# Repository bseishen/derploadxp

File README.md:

derploadxp
==========

Electronic Dummy Load

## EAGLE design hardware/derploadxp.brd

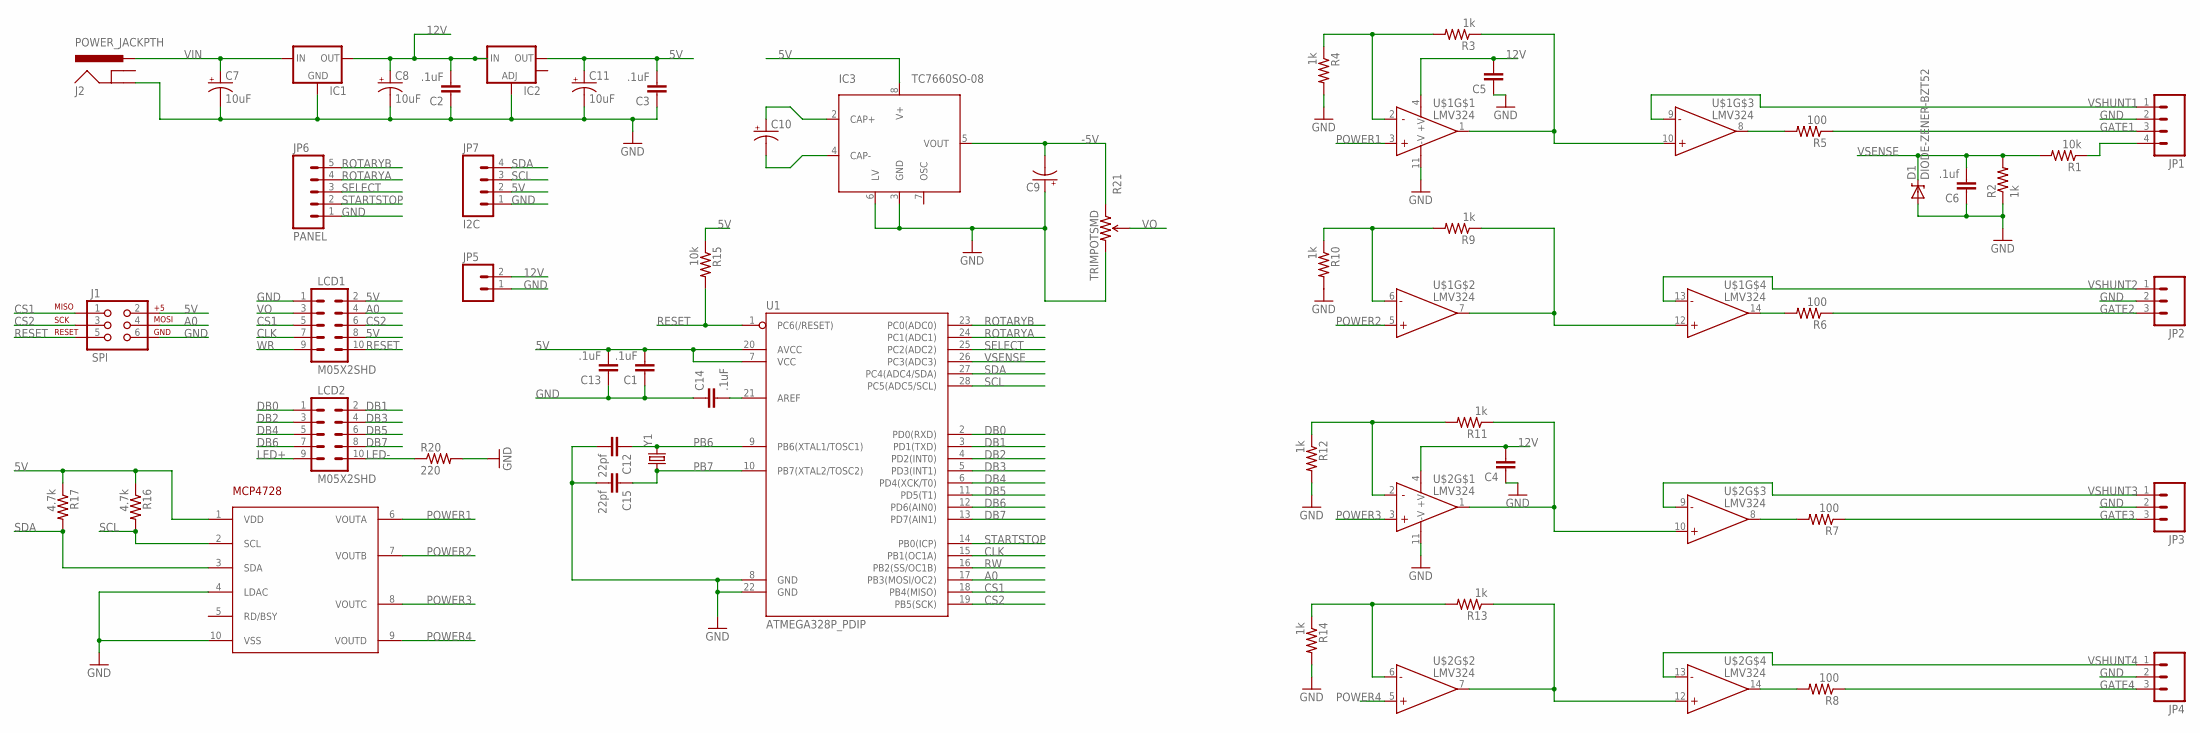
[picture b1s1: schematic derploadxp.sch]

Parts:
C1, C2, C3, C13, C14: .1uF; 0805
C4, C5: CAP0805; 0805
C6: .1uf; 0805
C7, C8, C11: 10uF; PANASONIC_C
C9, C10: CAP_POLC; PANASONIC_C
C12, C15: 22pf; 0805
D1: DIODE-ZENER-BZT52; SOD-323
IC1: V_REG_78XXSINK; TO220-IGO
IC2: V_REG_LM1117SOT223; SOT223
IC3: TC7660SO-08; SO-08
J1: SPI; 2X3-NS
J2: POWER_JACKPTH; POWER_JACK_PTH
JP1: M04LOCK; 1X04_LOCK
JP2, JP3, JP4: M03LOCK; 1X03_LOCK
JP5: M02LOCK; 1X02_LOCK
JP6: PANEL; 1X05_LOCK
JP7: I2C; 1X04_LOCK
LCD1, LCD2: M05X2SHD; 2X5-SHROUDED
R1, R15: 10k; 0805
R2, R3, R4, R9, R10, R11, R12, R13, R14: 1k; 0805
R5, R6, R7, R8: 100; 0805
R16, R17: 4.7k; 0805
R20: 220; 0805
R21: TRIMPOTSMD; TRIMPOT-3MM
U1: ATMEGA328P_PDIP; DIL28-3
U$1, U$2: LMV324; SO014
U$4: MCP4728; MSOP10
Y1: CRYSTALSMD; HC49UP

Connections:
5V: C1.2, C3.2, C11.+, C13.2, IC2.2 (OUT), IC3.8 (V+), J1.2, JP7.2, LCD1.2, LCD1.8, R15.1, R16.1, R17.1, U1.7 (VCC), U1.20 (AVCC), U$4.1 (VDD)
12V: C2.2, C4.2, C5.2, C8.+, IC1.OUT, IC2.3 (IN), JP5.2, U$1.4 (+V), U$2.4 (+V)
-5V: C9.-, IC3.5 (VOUT), R21.1 (CCW)
A0: J1.4, LCD1.4, U1.17 (PB3(MOSI/OC2))
CLK: LCD1.7, U1.15 (PB1(OC1A))
CS1: J1.1, LCD1.5, U1.18 (PB4(MISO))
CS2: J1.3, LCD1.6, U1.19 (PB5(SCK))
DB0: LCD2.1, U1.2 (PD0(RXD))
DB1: LCD2.2, U1.3 (PD1(TXD))
DB2: LCD2.3, U1.4 (PD2(INT0))
DB3: LCD2.4, U1.5 (PD3(INT1))
DB4: LCD2.5, U1.6 (PD4(XCK/T0))
DB5: LCD2.6, U1.11 (PD5(T1))
DB6: LCD2.7, U1.12 (PD6(AIN0))
DB7: LCD2.8, U1.13 (PD7(AIN1))
GATE1: JP1.3, R5.1
GATE2: JP2.3, R6.1
GATE3: JP3.3, R7.1
GATE4: JP4.3, R8.1
GND: C1.1, C2.1, C3.1, C4.1, C5.1, C6.1, C7.-, C8.-, C9.+, C11.-, C12.2, C13.1, C14.1, C15.2, D1.2 (A), IC1.GND, IC2.1 (ADJ), IC3.3 (GND), IC3.6 (LV), J1.6, J2.GND, JP1.2, JP2.2, JP3.2, JP4.2, JP5.1, JP6.1, JP7.1, LCD1.1, R2.1, R4.2, R10.2, R12.2, R14.2, R20.2, R21.3 (CW), U1.8 (GND), U1.22 (GND), U$1.11 (-V), U$2.11 (-V), U$4.4 (LDAC), U$4.10 (VSS)
LED+: LCD2.9
LED-: LCD2.10, R20.1
unnamed: JP1.4, R1.1
unnamed: C10.+, IC3.2 (CAP+)
unnamed: R5.2, U$1.8 (OUT)
unnamed: C10.-, IC3.4 (CAP-)
unnamed: R3.1, U$1.1 (OUT), U$1.10 (+IN)
unnamed: R9.2, R10.1, U$1.6 (-IN)
unnamed: R3.2, R4.1, U$1.2 (-IN)
unnamed: R6.2, U$1.14 (OUT)
unnamed: R8.2, U$2.14 (OUT)
unnamed: R7.2, U$2.8 (OUT)
unnamed: C14.2, U1.21 (AREF)
unnamed: R9.1, U$1.7 (OUT), U$1.12 (+IN)
unnamed: R11.2, R12.1, U$2.2 (-IN)
unnamed: R13.2, R14.1, U$2.6 (-IN)
unnamed: R13.1, U$2.7 (OUT), U$2.12 (+IN)
unnamed: R11.1, U$2.1 (OUT), U$2.10 (+IN)
PB6: C12.1, U1.9 (PB6(XTAL1/TOSC1)), Y1.2
PB7: C15.1, U1.10 (PB7(XTAL2/TOSC2)), Y1.1
POWER1: U$1.3 (+IN), U$4.6 (VOUTA)
POWER2: U$1.5 (+IN), U$4.7 (VOUTB)
POWER3: U$2.3 (+IN), U$4.8 (VOUTC)
POWER4: U$2.5 (+IN), U$4.9 (VOUTD)
RESET: J1.5, LCD1.10, R15.2, U1.1 (PC6(/RESET))
ROTARYA: JP6.4, U1.24 (PC1(ADC1))
ROTARYB: JP6.5, U1.23 (PC0(ADC0))
RW: U1.16 (PB2(SS/OC1B))
SCL: JP7.3, R16.2, U1.28 (PC5(ADC5/SCL)), U$4.2 (SCL)
SDA: JP7.4, R17.2, U1.27 (PC4(ADC4/SDA)), U$4.3 (SDA)
SELECT: JP6.3, U1.25 (PC2(ADC2))
STARTSTOP: JP6.2, U1.14 (PB0(ICP))
VIN: C7.+, IC1.IN, J2.PWR
VO: LCD1.3, R21.2 (WIPER)
VSENSE: C6.2, D1.1 (C), R1.2, R2.2, U1.26 (PC3(ADC3))
VSHUNT1: JP1.1, U$1.9 (-IN)
VSHUNT2: JP2.1, U$1.13 (-IN)
VSHUNT3: JP3.1, U$2.9 (-IN)
VSHUNT4: JP4.1, U$2.13 (-IN)
WR: LCD1.9

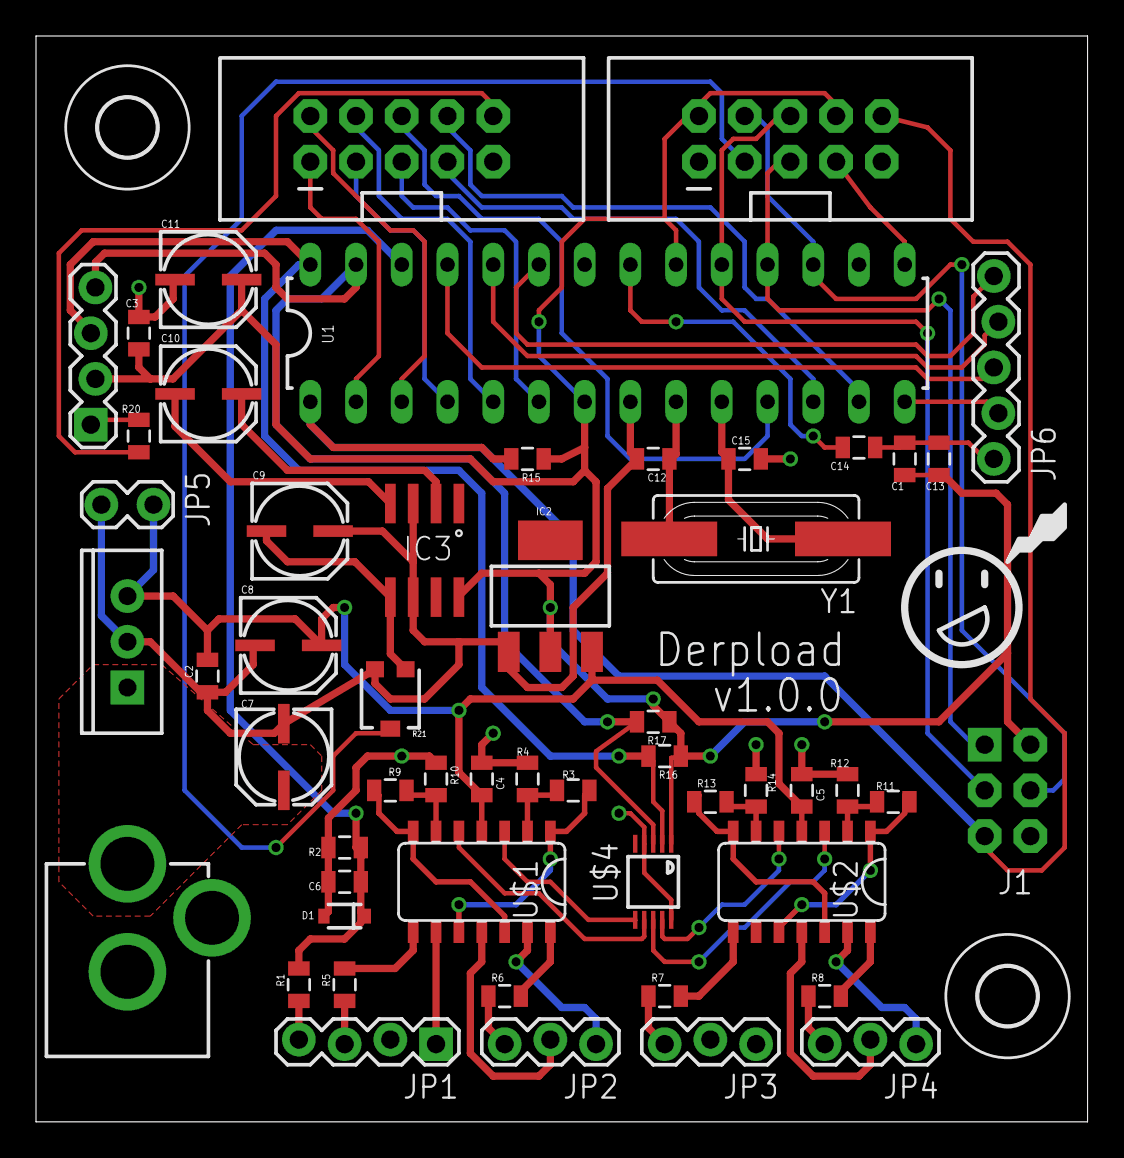
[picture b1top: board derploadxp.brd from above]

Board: 2 copper layers, 58.4 x 60.3 mm, 56 parts (0 on the bottom side), 57 nets.

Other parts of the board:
U$5, U$7: 3,2

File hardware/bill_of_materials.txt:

Partlist

Exported from derploadxp.brd at 10/17/13 11:35 PM

EAGLE Version 6.4.0 Copyright (c) 1988-2013 CadSoft

Assembly variant: 

Part     Value             Package        Library                    Position (inch)       Orientation

C1       .1uF              0805           SparkFun-Passives          (1.9 1.45)            R270
C2       .1uF              0805           SparkFun-Passives          (0.375 0.975)         R90
C3       .1uF              0805           SparkFun-Passives          (0.225 1.725)         R270
C4                         0805           SparkFun-Passives          (0.975 0.75)          R270
C5                         0805           SparkFun-Passives          (1.675 0.725)         R270
C6       .1uf              0805           SparkFun-Passives          (0.675 0.525)         R0
C7       10uF              PANASONIC_C    SparkFun-Capacitors        (0.55 0.8)            R270
C8       10uF              PANASONIC_C    SparkFun-Capacitors        (0.55 1.05)           R0
C9                         PANASONIC_C    SparkFun-Capacitors        (0.575 1.3)           R0
C10                        PANASONIC_C    SparkFun-Capacitors        (0.375 1.6)           R0
C11      10uF              PANASONIC_C    SparkFun-Capacitors        (0.375 1.85)          R0
C12      22pf              0805           SparkFun-Passives          (1.35 1.45)           R180
C13      .1uF              0805           SparkFun-Passives          (1.975 1.45)          R270
C14      .1uF              0805           SparkFun-Passives          (1.8 1.475)           R180
C15      22pf              0805           SparkFun-Passives          (1.55 1.45)           R0
D1       DIODE-ZENER-BZT52 SOD-323        SparkFun-DiscreteSemi      (0.675 0.45)          R180
IC1                        TO220-IGO      SparkFun-PowerIC           (0.2 1.05)            R90
IC2                        SOT223         SparkFun-PowerIC           (1.125 1.15)          R0
IC3      TC7660SO-08       SO-08          microchip_tc7660           (0.85 1.25)           R180
J1       SPI               2X3-NS         SparkFun-Connectors        (2.125 0.725)         R270
J2       POWER_JACKPTH     POWER_JACK_PTH SparkFun-Connectors        (0.2 0.025)           R0
JP1                        1X04_LOCK      SparkFun-Connectors        (0.875 0.175)         R180
JP2                        1X03_LOCK      SparkFun-Connectors        (1.225 0.175)         R180
JP3                        1X03_LOCK      SparkFun-Connectors        (1.575 0.175)         R180
JP4                        1X03_LOCK      SparkFun-Connectors        (1.925 0.175)         R180
JP5                        1X02_LOCK      SparkFun-Connectors        (0.15 1.35)           R0
JP6      PANEL             1X05_LOCK      SparkFun-Connectors        (2.1 1.45)            R90
JP7      I2C               1X04_LOCK      SparkFun-Connectors        (0.125 1.525)         R90
LCD1     M05X2SHD          2X5-SHROUDED   SparkFun-Connectors        (1.65 2.15)           R90
LCD2     M05X2SHD          2X5-SHROUDED   SparkFun-Connectors        (0.8 2.15)            R90
R1       10k               0805           SparkFun-Passives          (0.575 0.3)           R90
R2       1k                0805           SparkFun-Passives          (0.675 0.6)           R0
R3       1k                0805           SparkFun-Passives          (1.175 0.725)         R180
R4       1k                0805           SparkFun-Passives          (1.075 0.75)          R90
R5       100               0805           SparkFun-Passives          (0.675 0.3)           R90
R6       100               0805           SparkFun-Passives          (1.025 0.275)         R0
R7       100               0805           SparkFun-Passives          (1.375 0.275)         R0
R8       100               0805           SparkFun-Passives          (1.725 0.275)         R0
R9       1k                0805           SparkFun-Passives          (0.775 0.725)         R0
R10      1k                0805           SparkFun-Passives          (0.875 0.75)          R90
R11      1k                0805           SparkFun-Passives          (1.875 0.7)           R180
R12      1k                0805           SparkFun-Passives          (1.775 0.725)         R90
R13      1k                0805           SparkFun-Passives          (1.475 0.7)           R0
R14      1k                0805           SparkFun-Passives          (1.575 0.725)         R90
R15      10k               0805           SparkFun-Passives          (1.075 1.45)          R180
R16      4.7k              0805           SparkFun-Passives          (1.375 0.8)           R180
R17      4.7k              0805           SparkFun-Passives          (1.35 0.875)          R180
R20      220               0805           SparkFun-Passives          (0.225 1.5)           R90
R21      TRIMPOTSMD        TRIMPOT-3MM    SparkFun-Electromechanical (0.775 0.925)         R180
U$1      LMV324            SO014          SparkFun-AnalogIC          (1 0.525)             R180
U$2      LMV324            SO014          SparkFun-AnalogIC          (1.7 0.525)           R180
U$4      MCP4728           MSOP10         mcp4728                    (1.35 0.525)          R180
U1       ATMEGA328P_PDIP   DIL28-3        SparkFun-DigitalIC         (1.25 1.725)          R0
Y1                         HC49UP         SparkFun-FreqCtrl          (1.575 1.275)         R180

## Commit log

2013-09-25 added .gitignore file, set to ignore *.b#* and *.s#*
2013-09-25 Moved necessary libaries to separate library directory
2013-09-25 updated schematic to support better board layout by moving DB0-7 Pins, corrected DB8 to be RESET
2013-09-26 Added design rules for PCB verification for two potential PCB mfg.
2013-09-26 Init software commit
    This first commit of software is very unpolished. Still lacking I2C
    comms to the DAC atm.
2013-09-26 added structure to support hardware andsoftware of the project
2013-09-26 changed pcb manufacturer rules to markdown and removed unecessary files
2013-09-26 Started change log to resolve Issue #6
2013-09-26 added vim swp files to the ignore list
2013-09-26 Resolving Issue #9 adding all missing Sparkfun libraries
2013-09-26 Resolved Issue #1 and #2 moved items around to add project name and version to top layer silkscreen
2013-09-26 Added one of two mounting holes to resolve Issue #3
2013-09-26 Added two of two mounting holes to resolve Issue #3
2013-09-26 moving documentation to project root
2013-09-26 corrected errors in the markdown causing the software and documentation section to not show
2013-09-27 Added required arduino libraries. All kinds of DAC fun. Still in super Alpha stage, and very messy!
2013-09-27 Pin change library added
2013-09-30 Added 12V aux port
    Addresses issue #11
2013-10-14 Added PDF and placed fan port on Board
2013-10-18 rearranged and corrected visible silkscreen for component values and names to solve Issue #8
2013-10-18 added missing junctions and corrected other necessary errors, remainder were approved resolving Issue #10
2013-10-18 added bill of materials to resolve Issue #7
2013-10-25 Poured ground plane. Sent to osh park.

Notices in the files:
parts and their libraries:
SparkFun-DigitalIC: Licensing: CC v3.0 Share-Alike You are welcome to use this library for commercial purposes.
